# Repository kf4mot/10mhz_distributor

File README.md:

# 10mhz_distributor
A 10 MHz 3 channel distribution amplifier and low pass filter designed to integrate into a BG7TBL GPSDO. A 5th. order LPF on both the input and outputs allows it to be driven with either sine or square waves and produce a sine output of around 12 dBm into a 50Ω load.
Power consumption is about 130 mA @12V.

[Schematic](https://github.com/kf4mot/10mhz_distributor/blob/master/hardware/10mhz_distributor_r1.pdf)

[Created with KiCAD ver. 5.1.5-3](https://kicad.org)

**Notes worth reading**

1. Schematic and BOM show The Qorvo TQP369182 as the MMIC. TQP369180 was actually used on the first board. The extra gain of the 182 seems unnecessary when driven with a 5V square wave and it may cause oscillation based on past experience. Bias resistors remain at 91Ω. Upgrade at your own risk and let me know how it goes if you try it or any other MMIC.
1. Pads for a optional attn. are on the input. *Trace that shorts R2 should be cut.* **Untested.**
1. Pads for a optional isolation transformer are on the 3rd. output. **Untested.**
1. Jitter and delay/phase shift are untested, but assumed good enough for a inexpensive GPSDO. If you build it and have the lab to test please share your results.
1. I left the input BNC (J3) off of mine and ran a internal wire to the GPSDO output. The BNC could be added by those that want the option to loop the clock or any other suitable input back into the distribution amp. Or those that want to use this as a stand alone general purpose distribution amp.
1. The 50Ω input load (R11) is 0603 size because I happen to have it in my inventory. You could use a 1206 at the R1 position if prefered. Or probably left off altogether if you're driving with a sinewave and bypassing the input filter.
   
Attenuator table for 1% resistors
Attn. |R2 | R1, R3
------------ | ------------- | ---------
3 dB| 17.8Ω | 294Ω
6 dB| 37.4Ω | 150Ω
10 dB | 71.5Ω | 95.3Ω

[Attenuator Calc](https://www.pasternack.com/t-calculator-pi-attn.aspx)

[Licensed under CERN-OHL-S V2. Julian White, 2020](https://www.ohwr.org/project/cernohl/wikis/home)

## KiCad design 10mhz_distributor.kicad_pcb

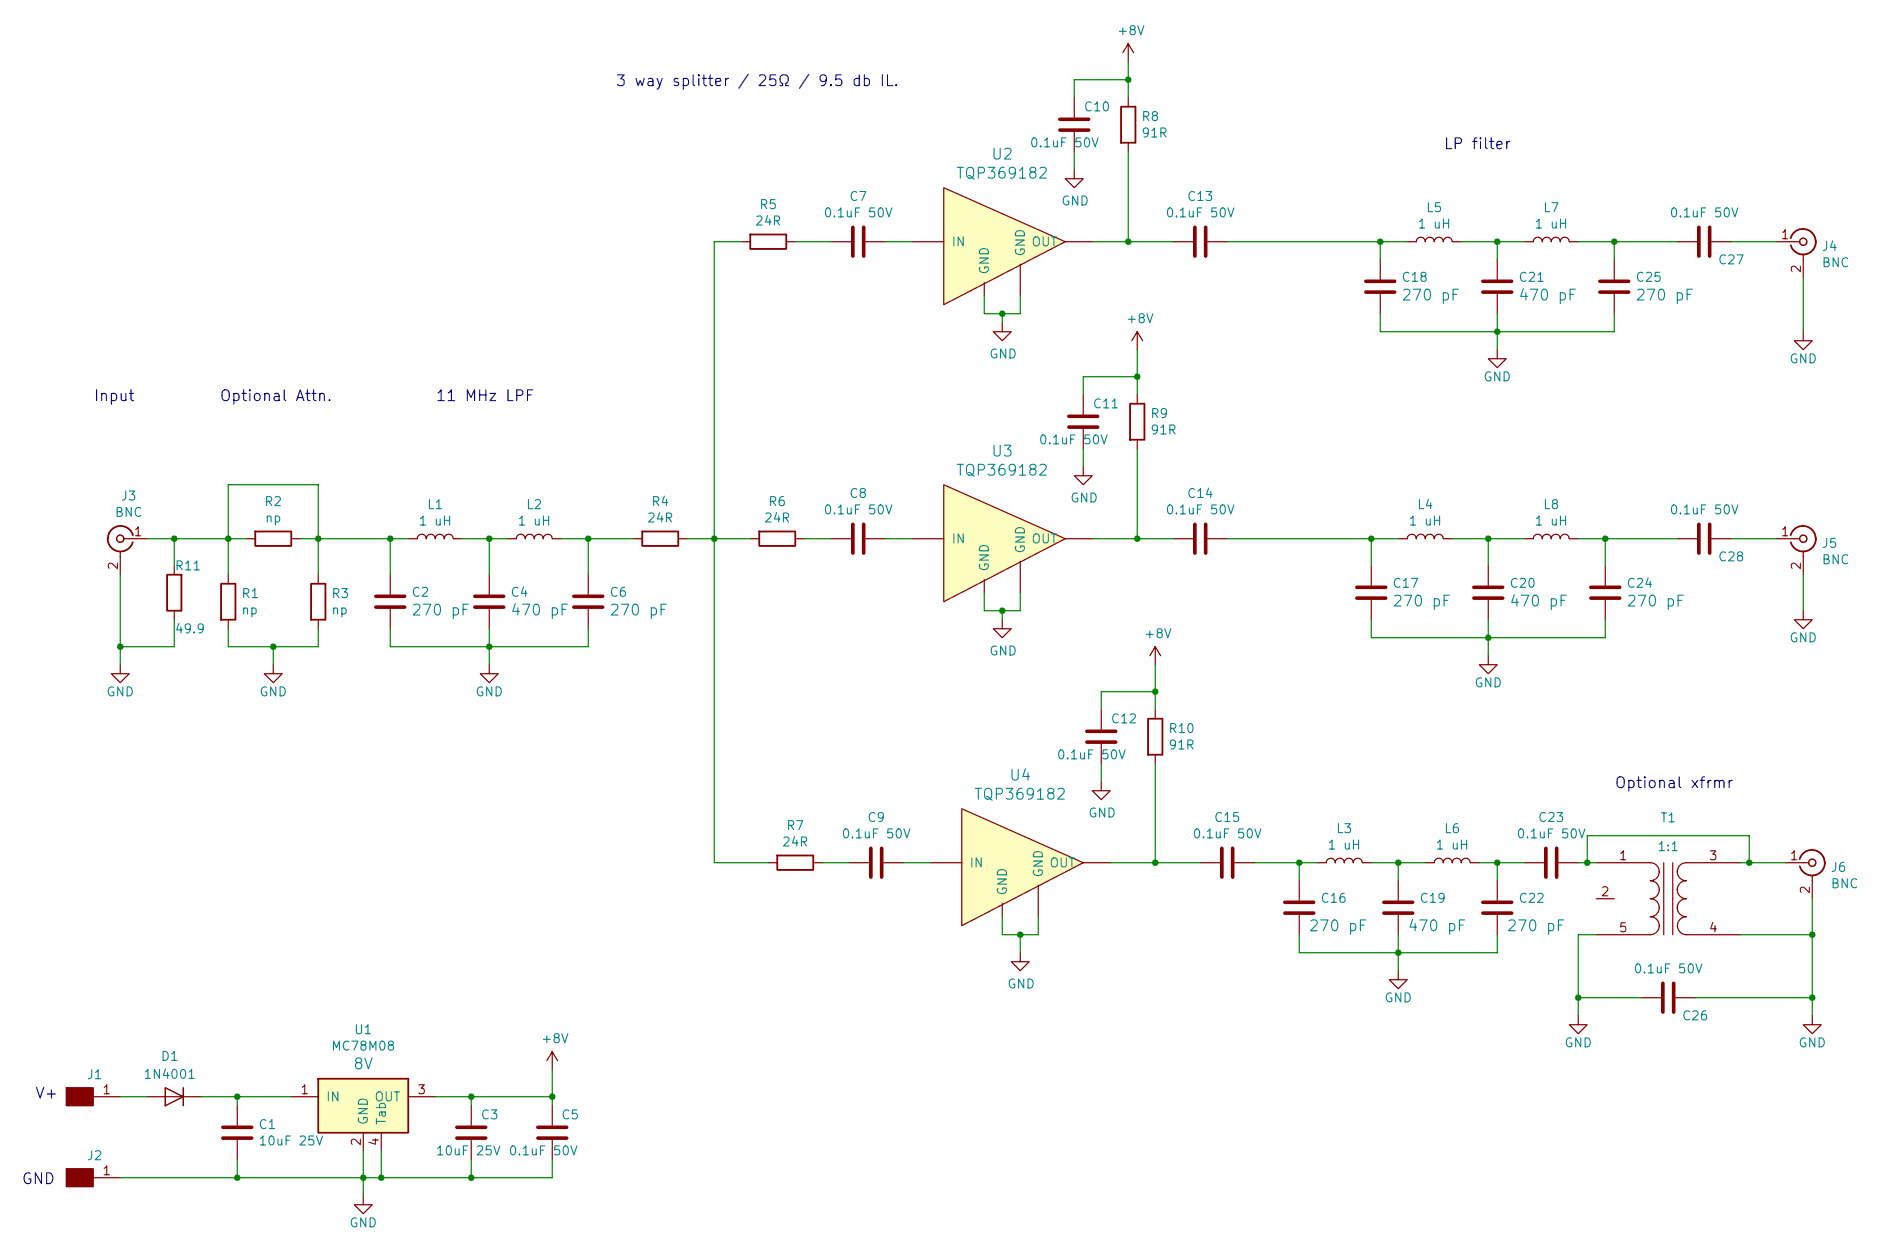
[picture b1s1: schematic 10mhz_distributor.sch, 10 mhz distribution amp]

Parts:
C1, C3: 10uf_25V_1206; C_1206_3216Metric_Pad1.42x1.75mm_HandSolder; Part Number CGA5L1X7R1E106K160AC
C2, C6, C16, C17, C18, C22, C24, C25: C_270pF_1206_C0G; R_1206_3216Metric_Pad1.42x1.75mm_HandSolder; Part Number 12062A271JAT2A
C4, C19, C20, C21: C_470pF_1206_C0G; R_1206_3216Metric_Pad1.42x1.75mm_HandSolder; Part Number CC1206JRNPOYBN471
C5, C7, C8, C9, C10, C11, C12, C13, C14, C15, C23, C26, C27, C28: 0.1uF_50V_0805_x7r; C_0805_2012Metric_Pad1.15x1.40mm_HandSolder; Part Number C0805C104K5RACTU
D1: 1N4001; D_DO-41_SOD81_P2.54mm_Vertical_AnodeUp; Part Number 1N4004
J1, J2: Conn_5mm_pad; SolderWirePad_single_SMD_5mm
J3, J4, J5, J6: BNC_Molex_0731375003; bnc_molex_0731375003; Part Number 0731375003
L1, L2, L3, L4, L5, L6, L7, L8: L_1uh_2%_1008; L_1008; Part Number LQW2UAS1R0G0CL
R1, R2, R3: R_1206; R_1206_3216Metric_Pad1.42x1.75mm_HandSolder; Part Number np
R4, R5, R6, R7: R_24_sm1206; R_1206_3216Metric_Pad1.42x1.75mm_HandSolder; Part Number CR1206-FX-24R0ELF
R8, R9, R10: R_91_sm1206; R_1206_3216Metric_Pad1.42x1.75mm_HandSolder; Part Number RC1206FR-0791RL
R11: R_49R9_sm0603; R_0603_1608Metric_Pad1.05x0.95mm_HandSolder; Part Number RC0603FR-0749R9L
T1: Transformer_1_1_MABA_007159; MABA-007159_transformer; Part Number MABA-007159-000000
U1: MC78M08; TO-252-2; Part Number MC78M08CDTRKG
U2, U3, U4: TQP369182; SOT-89; Part Number TQP369182

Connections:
+8V: C3.1, C5.2, C10.2, C11.2, C12.2, R8.1, R9.1, R10.1, U1.3 (OUT)
GND: C1.2, C2.2, C3.2, C4.2, C5.1, C6.2, C10.1, C11.1, C12.1, C16.2, C17.2, C18.2, C19.2, C20.2, C21.2, C22.2, C24.2, C25.2, C26.1, C26.2, J2.1, J3.2 (Ext), J4.2 (Ext), J5.2 (Ext), J6.2 (Ext), R1.2, R3.2, R11.1, T1.4 (SA), T1.5 (AB), U1.2 (GND), U1.4 (Tab), U2.2 (GND), U2.4 (GND), U3.2 (GND), U3.4 (GND), U4.2 (GND), U4.4 (GND)
unnamed: C1.1, D1.1 (K), U1.1 (IN)
unnamed: C2.1, J3.1 (In), L1.1, R1.1, R2.1, R2.2, R3.1, R11.2
unnamed: C4.1, L1.2, L2.1
unnamed: C6.1, L2.2, R4.2
unnamed: C7.1, U2.1 (IN)
unnamed: C7.2, R5.1
unnamed: C8.1, U3.1 (IN)
unnamed: C8.2, R6.1
unnamed: C9.1, U4.1 (IN)
unnamed: C9.2, R7.1
unnamed: C13.1, C18.1, L5.1
unnamed: C13.2, R8.2, U2.3 (OUT)
unnamed: C14.1, C17.1, L4.1
unnamed: C14.2, R9.2, U3.3 (OUT)
unnamed: C15.1, C16.1, L3.1
unnamed: C15.2, R10.2, U4.3 (OUT)
unnamed: C19.1, L3.2, L6.1
unnamed: C20.1, L4.2, L8.1
unnamed: C21.1, L5.2, L7.1
unnamed: C22.1, C23.2, L6.2
unnamed: C23.1, J6.1 (In), T1.1 (AA), T1.3 (SB)
unnamed: C24.1, C28.2, L8.2
unnamed: C25.1, C27.2, L7.2
unnamed: C27.1, J4.1 (In)
unnamed: C28.1, J5.1 (In)
unnamed: D1.2 (A), J1.1
unnamed: R4.1, R5.2, R6.2, R7.2

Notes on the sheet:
GND
11 MHz LPF
LP filter
Optional Attn.
Input
3 way splitter / 25Ω / 9.5 db IL.
Optional xfrmr

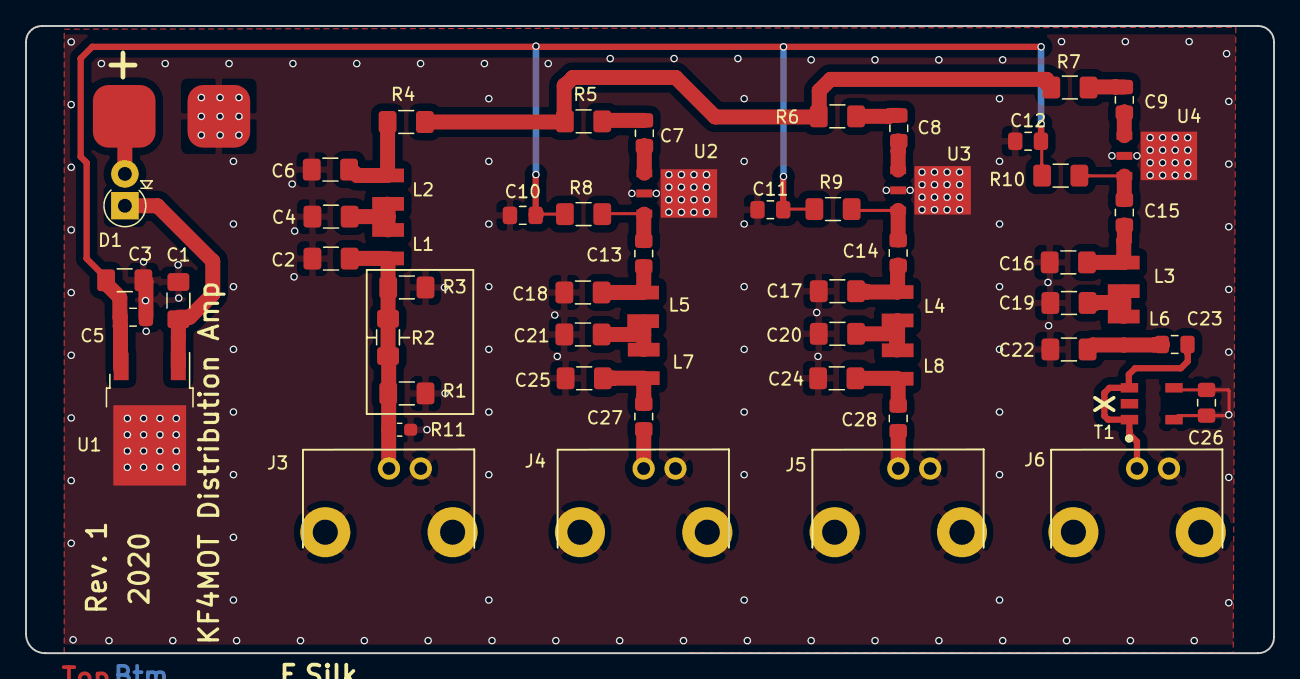
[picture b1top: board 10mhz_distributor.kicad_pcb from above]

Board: 2 copper layers, 99.6 x 50.0 mm, 59 parts (0 on the bottom side), 29 nets.

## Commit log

2020-03-27 Create images
2020-03-28 Create img
2020-03-28 Create hw
2020-03-28 Rename 10mhz_distributor.kicad_pcb to hardware/10mhz_distributor.kicad_pcb
2020-03-28 Rename 10mhz_distributor.pro to hardware/10mhz_distributor.pro
2020-03-28 Rename 10mhz_distributor.sch to hardware/10mhz_distributor.sch
2020-03-28 Rename sym-lib-table to hardware/sym-lib-table
2020-03-28 Create doc
2020-03-28 Create prod
2020-03-28 Create sim
2020-03-28 Create CAD
2020-03-28 Create firm
2020-03-28 Update firm
2020-03-31 Create LICENSE
2020-04-03 Rename LICENSE to LICENSE.md
2021-11-10 Update README.md
    https://forum.kicad.info/t/warning-avoid-all-links-to-kicad-pcb-org-use-kicad-org/31521
